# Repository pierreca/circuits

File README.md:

# circuits
Home-made electronics. It's probably full of mistakes but it's fun to learn.

## 4017-chaser
The simplest possible use of a 4017 IC with a 555 to clock it. Works with 10mm LEDs that I had on hand.

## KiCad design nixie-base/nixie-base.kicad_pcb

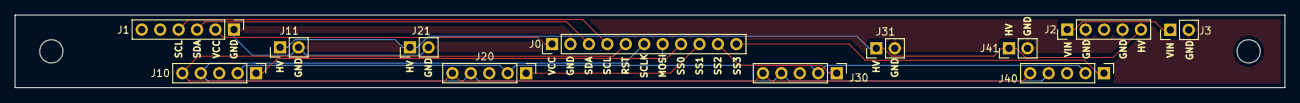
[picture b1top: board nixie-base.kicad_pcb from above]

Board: 2 copper layers, 175.0 x 10.0 mm, 12 parts (0 on the bottom side), 13 nets.

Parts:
J0: Arduino; PinHeader_1x11_P2.54mm_Vertical
J1: RTC; PinHeader_1x06_P2.54mm_Vertical
J2: PSU; PinHeader_1x05_P2.54mm_Vertical
J3: PWR_JACK; PinHeader_1x02_P2.54mm_Vertical
J10: TUBE_0; PinHeader_1x05_P2.54mm_Vertical
J11: TUBE_0_PWR; PinHeader_1x02_P2.54mm_Vertical
J20: TUBE_1; PinHeader_1x05_P2.54mm_Vertical
J21: TUBE_1_PWR; PinHeader_1x02_P2.54mm_Vertical
J30: TUBE_2; PinHeader_1x05_P2.54mm_Vertical
J31: TUBE_2_PWR; PinHeader_1x02_P2.54mm_Vertical
J40: TUBE_3; PinHeader_1x05_P2.54mm_Vertical
J41: TUBE_3_PWR; PinHeader_1x02_P2.54mm_Vertical

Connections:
GND: J0.2, J1.1, J2.2, J2.4, J3.2, J11.2, J21.2, J31.2, J41.2
HV: J2.5, J11.1, J21.1, J31.1, J41.1
MOSI: J0.7, J10.2, J20.2, J30.2, J40.2
RST: J0.5, J10.5, J20.5, J30.5, J40.5
SCL: J0.4, J1.4
SCLK: J0.6, J10.4, J20.4, J30.4, J40.4
SDA: J0.3, J1.3
SS0: J0.8, J10.1
SS1: J0.9, J20.1
SS2: J0.10, J30.1
SS3: J0.11, J40.1
VCC: J0.1, J1.2
VIN: J2.1, J3.1

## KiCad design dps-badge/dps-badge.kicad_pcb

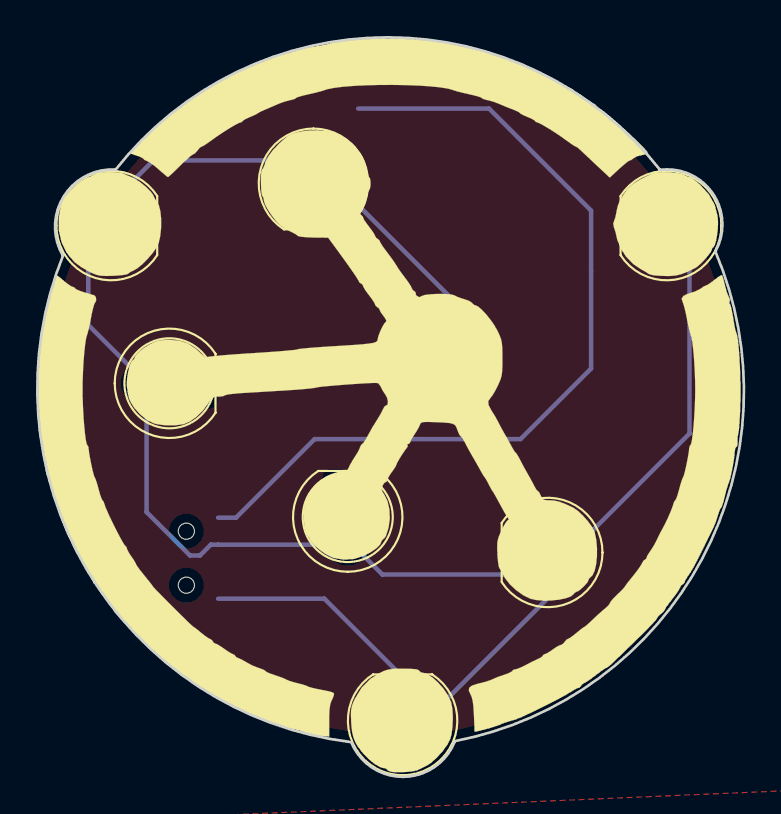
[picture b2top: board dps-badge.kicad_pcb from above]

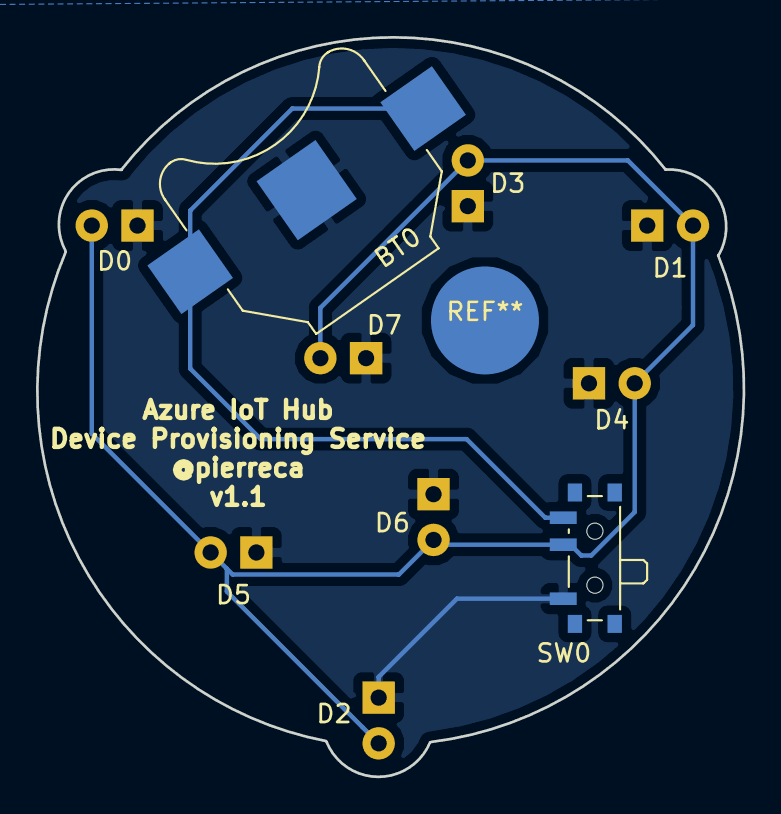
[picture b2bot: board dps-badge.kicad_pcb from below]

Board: 2 copper layers, 39.3 x 41.1 mm, 10 parts (2 on the bottom side), 3 nets.

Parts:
BT0: Battery_Cell; BatteryHolder_Keystone_3000_1x12mm
D0, D1, D2, D3, D4, D5, D6, D7: LED; LED_D5.0mm_FlatTop
SW0: SW_SPDT; SW_SPDT_PCM12

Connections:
GND: BT0.2, D0.1, D1.1, D2.1, D3.1, D4.1, D5.1, D6.1, D7.1, SW0.1
unnamed: BT0.1, SW0.3
unnamed: D0.2, D1.2, D2.2, D3.2, D4.2, D5.2, D6.2, D7.2, SW0.2

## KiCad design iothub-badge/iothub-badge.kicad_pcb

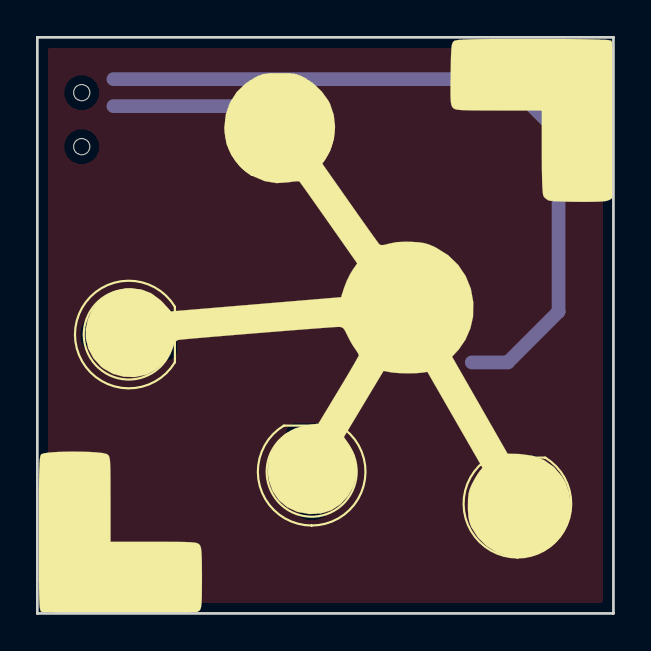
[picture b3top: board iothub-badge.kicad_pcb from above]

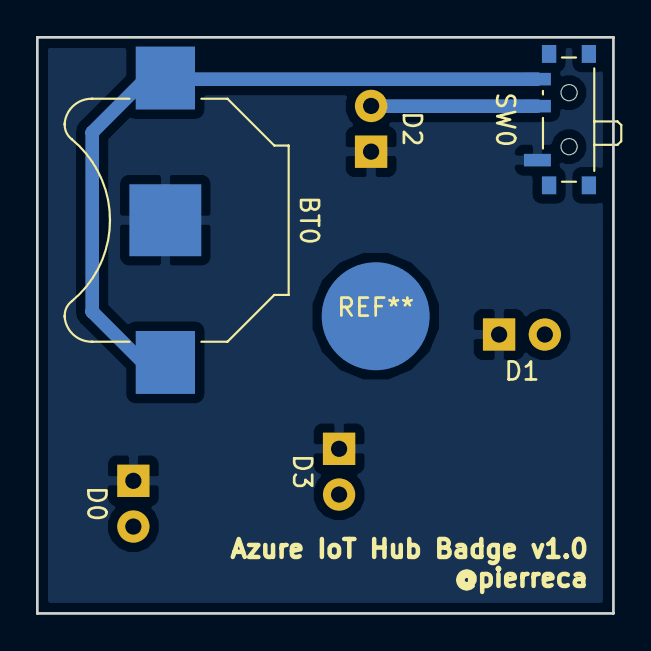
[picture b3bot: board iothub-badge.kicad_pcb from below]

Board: 2 copper layers, 32.0 x 32.0 mm, 6 parts (2 on the bottom side), 3 nets.

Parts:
BT0: Battery_Cell; BatteryHolder_Keystone_3000_1x12mm
D0, D1, D2, D3: LED; LED_D5.0mm_Clear
SW0: SW_SPDT; SW_SPDT_PCM12

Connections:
GND: BT0.2, D0.1, D1.1, D2.1, D3.1, SW0.1
unnamed: BT0.1, SW0.3
unnamed: D0.2, D1.2, D2.2, D3.2, SW0.2

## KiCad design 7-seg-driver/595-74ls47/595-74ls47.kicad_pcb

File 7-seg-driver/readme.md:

https://www.nutsvolts.com/magazine/article/using-seven-segment-displays-part-1

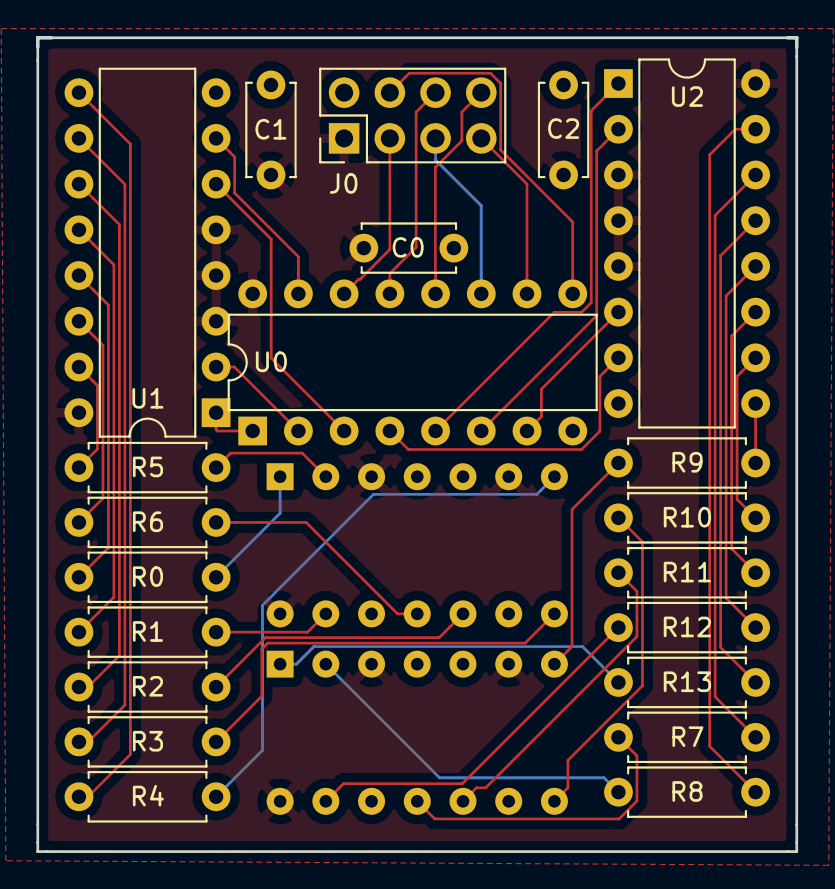
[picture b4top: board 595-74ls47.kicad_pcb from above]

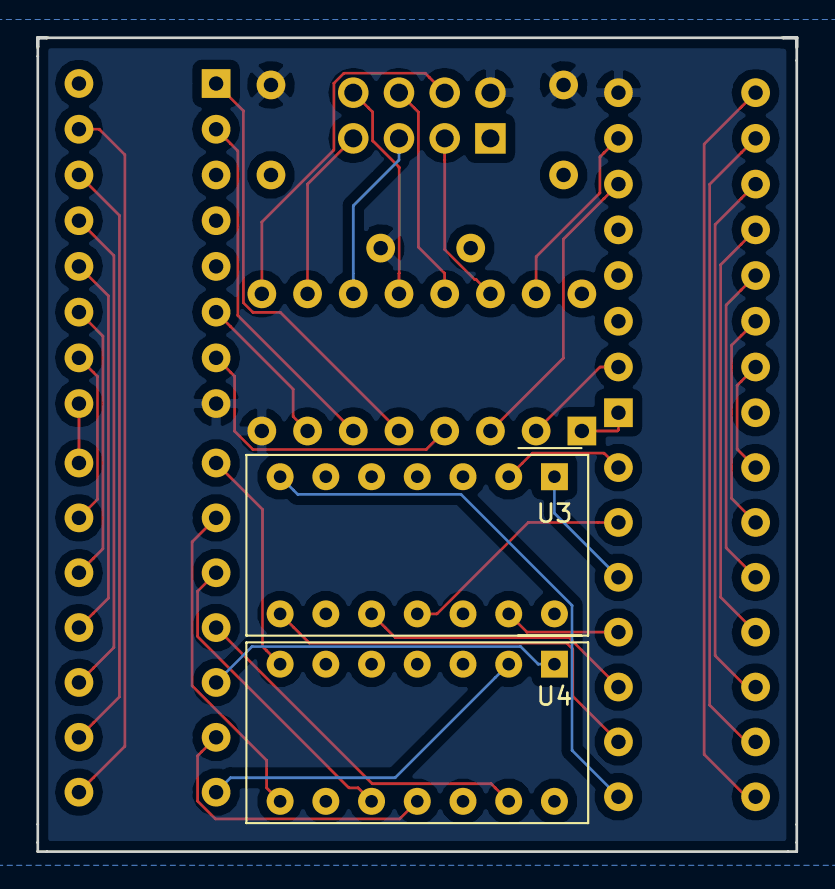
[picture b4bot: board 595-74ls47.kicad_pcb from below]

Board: 2 copper layers, 42.2 x 45.2 mm, 23 parts (2 on the bottom side), 44 nets.

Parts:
C0, C1, C2: 0.1uF; C_Disc_D5.0mm_W2.5mm_P5.00mm
J0: Conn_02x04_Odd_Even; PinHeader_2x04_P2.54mm_Vertical
R0, R1, R2, R3, R4, R5, R6, R7, R8, R9, R10, R11, R12, R13: 220; R_Axial_DIN0207_L6.3mm_D2.5mm_P7.62mm_Horizontal
U0: 74HC595; DIP-16_W7.62mm
U1, U2: 74LS47; DIP-16_W7.62mm
U3, U4: MAN72A

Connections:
GND: C0.1, C1.2, C2.2, J0.2, U0.8, U1.8, U2.8
unnamed: C0.2, C1.1, C2.1, J0.1, U0.16, U1.3, U1.4, U1.5, U1.16, U2.3, U2.4, U2.5, U2.16, U3.3, U3.6, U3.14, U4.3, U4.6, U4.14
unnamed: J0.3, U0.14
unnamed: J0.4, U0.9
unnamed: J0.5, U0.11
unnamed: J0.6, U0.13
unnamed: J0.7, U0.10
unnamed: J0.8, U0.12
unnamed: R0.1, U3.1
unnamed: R0.2, U1.13
unnamed: R1.1, U3.13
unnamed: R1.2, U1.12
unnamed: R2.1, U3.10
unnamed: R2.2, U1.11
unnamed: R3.1, U3.8
unnamed: R3.2, U1.10
unnamed: R4.1, U3.7
unnamed: R4.2, U1.9
unnamed: R5.1, U3.2
unnamed: R5.2, U1.15
unnamed: R6.1, U3.11
unnamed: R6.2, U1.14
unnamed: R7.1, U4.11
unnamed: R7.2, U2.14
unnamed: R8.1, U4.2
unnamed: R8.2, U2.15
unnamed: R9.1, U4.7
unnamed: R9.2, U2.9
unnamed: R10.1, U4.8
unnamed: R10.2, U2.10
unnamed: R11.1, U4.10
unnamed: R11.2, U2.11
unnamed: R12.1, U4.13
unnamed: R12.2, U2.12
unnamed: R13.1, U4.1
unnamed: R13.2, U2.13
unnamed: U0.1, U1.1
unnamed: U0.2, U1.2
unnamed: U0.3, U1.6
unnamed: U0.4, U2.7
unnamed: U0.5, U2.1
unnamed: U0.6, U2.2
unnamed: U0.7, U2.6
unnamed: U0.15, U1.7

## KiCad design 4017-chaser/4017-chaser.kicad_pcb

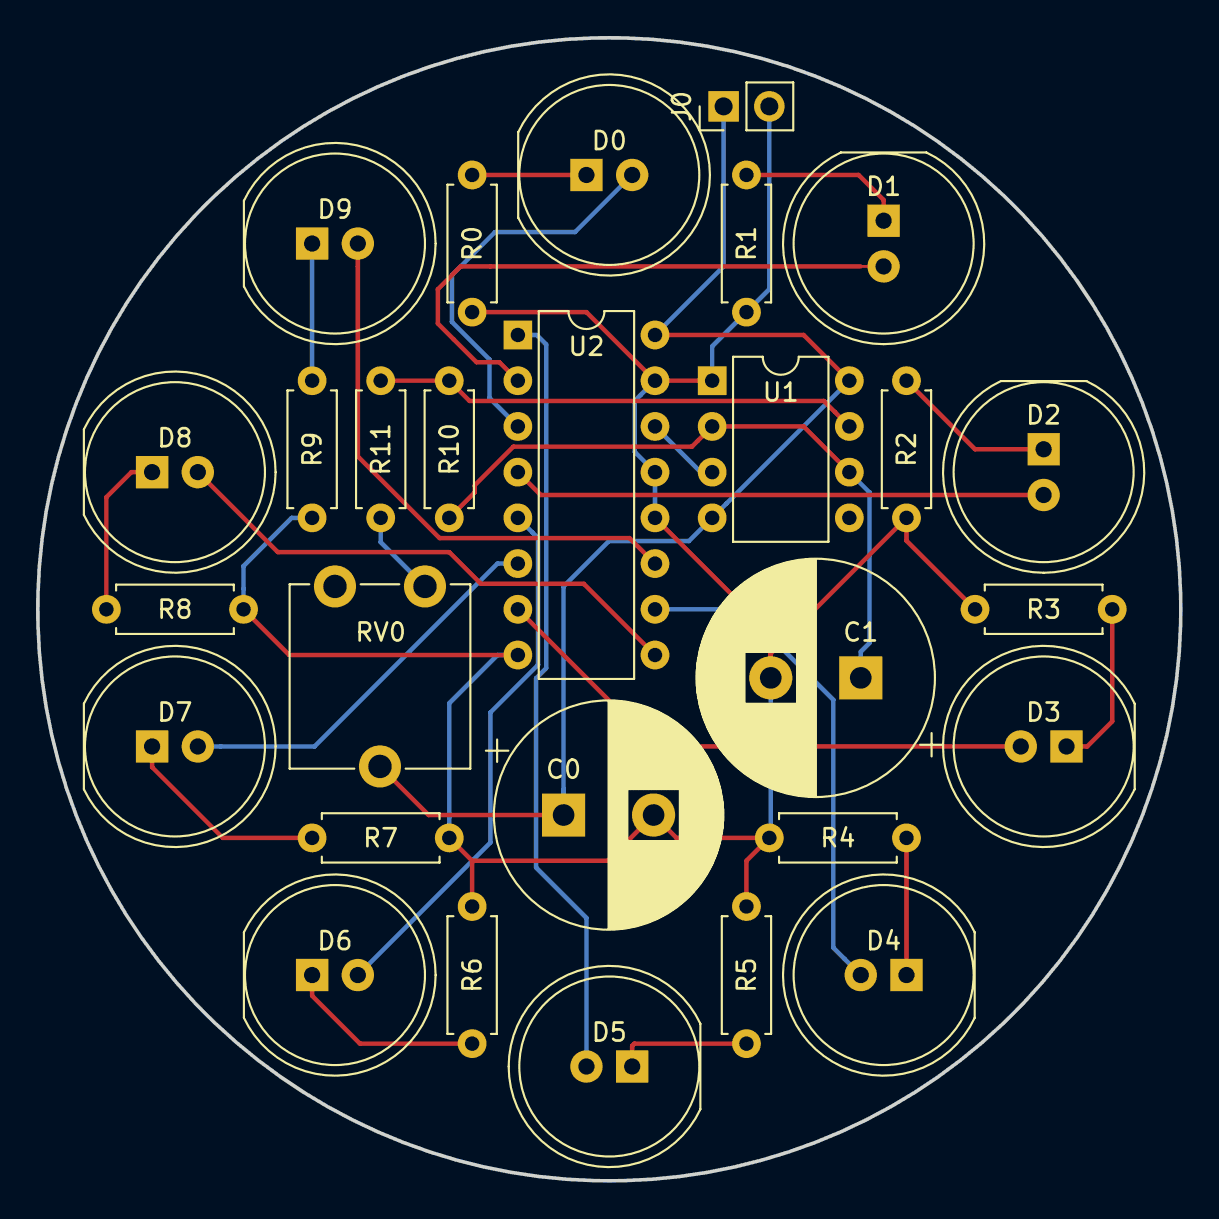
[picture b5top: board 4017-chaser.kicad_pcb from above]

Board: 2 copper layers, 63.5 x 63.5 mm, 28 parts (0 on the bottom side), 26 nets.

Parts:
C0: 100uF; CP_Radial_D12.5mm_P5.00mm
C1: 2.2uF; CP_Radial_D13.0mm_P5.00mm
D0, D1, D2, D3, D4, D5, D6, D7, D8, D9: LED; LED_D10.0mm
J0: Batt; PinHeader_1x02_P2.54mm_Vertical
R0, R1, R2, R3, R4, R5, R6, R7, R8, R9: 330; R_Axial_DIN0207_L6.3mm_D2.5mm_P7.62mm_Horizontal
R10, R11: 10k; R_Axial_DIN0207_L6.3mm_D2.5mm_P7.62mm_Horizontal
RV0: 500k; Potentiometer_ACP_CA9-V10_Vertical
U1: LMC555xN; DIP-8_W7.62mm
U2: 4017; DIP-16_W7.62mm

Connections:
GND: C0.2, C1.2, J0.2, R0.1, R1.1, R2.1, R3.1, R4.1, R5.1, R6.1, R7.1, R8.1, R9.1, U1.1, U2.8, U2.12, U2.13, U2.15
unnamed: C0.1, J0.1, RV0.2, U1.4, U1.8, U2.16
unnamed: C1.1, R10.1, U1.2, U1.6
unnamed: D0.1, R0.2
unnamed: D0.2, U2.3
unnamed: D1.1, R1.2
unnamed: D1.2, U2.2
unnamed: D2.1, R2.2
unnamed: D2.2, U2.4
unnamed: D3.1, R3.2
unnamed: D3.2, U2.7
unnamed: D4.1, R4.2
unnamed: D4.2, U2.10
unnamed: D5.1, R5.2
unnamed: D5.2, U2.1
unnamed: D6.1, R6.2
unnamed: D6.2, U2.5
unnamed: D7.1, R7.2
unnamed: D7.2, U2.6
unnamed: D8.1, R8.2
unnamed: D8.2, U2.9
unnamed: D9.1, R9.2
unnamed: D9.2, U2.11
unnamed: R10.2, R11.2, U1.7
unnamed: R11.1, RV0.3
unnamed: U1.3, U2.14

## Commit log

2018-11-22 initial commit of the 4017 chaser circuit
2018-12-10 add 595 and logo badges circuits - The 595 circuit routing is wrong: the digits are reversed (this can be fixed in software as demonstrated in the ino file) - The logo badges have not been tes
2019-09-03 basic code for neopixel clock + adjustments to dps badge + chronodot lib + nixie clock base
2019-09-08 Updated version of the neopixel clock code
2019-09-08 add v-carve files for cnc milling of the clock face
2019-09-08 Add base file for neopixel clock
2019-09-09 Add tabs to neopixel clock base
2019-09-09 add 2 pushbuttons to neopixel clock pcb design
2019-09-20 Add round base for neopixel clock
